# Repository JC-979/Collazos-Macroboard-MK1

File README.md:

# Collazos-Macroboard-MK1
This is the first Macroboard that i have made, and this made me interested on the all the hack club stuff, hope this project is just the beggining of a path with Blueprint
## Bom

- 9x Cherry MX Switches
- 3x SK6812 MINI Leds
- 1x XIAO RP2040
- 9x Blank DSA Keycaps
- 9x M3x16 Bolt
- 9x M3 Heatset

## Screenshots

## Overall Hackpad

- 
- 

## Schematics

- 

## PCB

- 

## Case

- 
- 
-

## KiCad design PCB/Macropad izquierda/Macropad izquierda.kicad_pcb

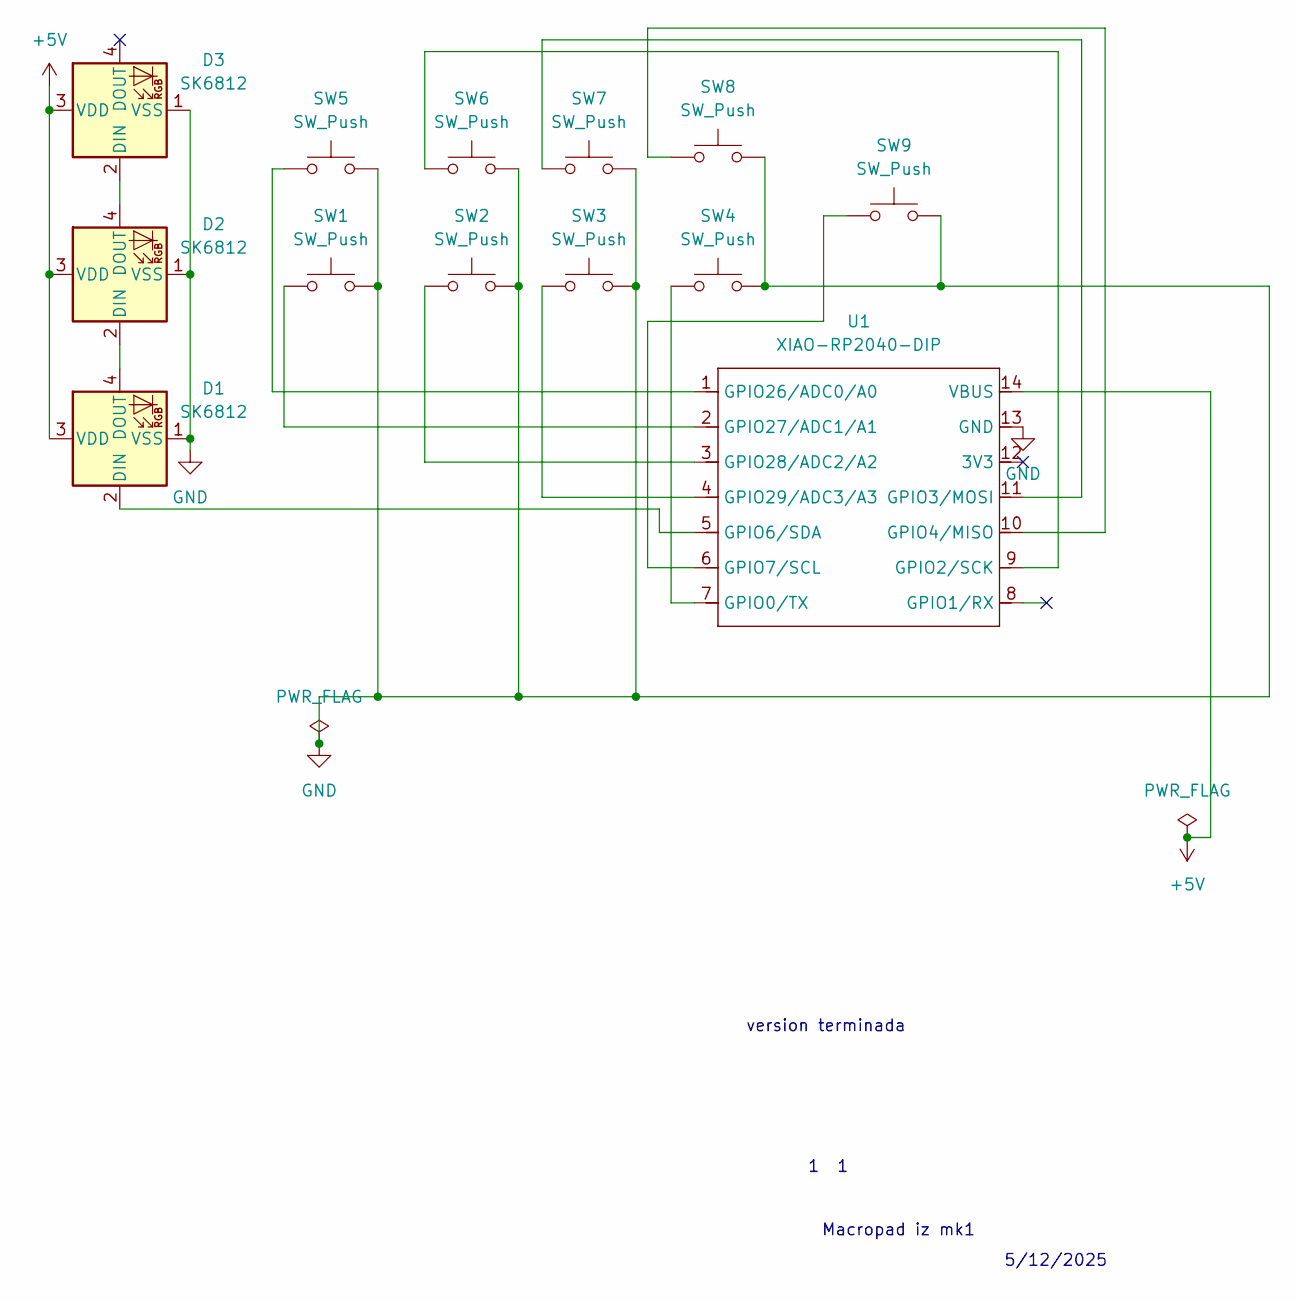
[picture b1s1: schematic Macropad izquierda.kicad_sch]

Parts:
D1, D2, D3: SK6812; LED_SK6812_PLCC4_5.0x5.0mm_P3.2mm
SW1, SW2, SW3, SW4, SW5, SW6, SW7, SW8, SW9: SW_Push; SW_Cherry_MX_1.00u_PCB
U1: XIAO-RP2040-DIP

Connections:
+5V: D1.3 (VDD), D2.3 (VDD), D3.3 (VDD), U1.14 (VBUS)
GND: D1.1 (VSS), D2.1 (VSS), D3.1 (VSS), SW1.2, SW2.2, SW3.2, SW4.2, SW5.2, SW6.2, SW7.2, SW8.2, SW9.2, U1.13 (GND)
unnamed: D1.2 (DIN), U1.5 (GPIO6/SDA)
unnamed: D1.4 (DOUT), D2.2 (DIN)
unnamed: D2.4 (DOUT), D3.2 (DIN)
unnamed: SW4.1, U1.7 (GPIO0/TX)
unnamed: SW6.1, U1.9 (GPIO2/SCK)
unnamed: SW7.1, U1.11 (GPIO3/MOSI)
unnamed: SW8.1, U1.10 (GPIO4/MISO)
unnamed: SW9.1, U1.6 (GPIO7/SCL)
unnamed: SW5.1, U1.1 (GPIO26/ADC0/A0)
unnamed: SW1.1, U1.2 (GPIO27/ADC1/A1)
unnamed: SW2.1, U1.3 (GPIO28/ADC2/A2)
unnamed: SW3.1, U1.4 (GPIO29/ADC3/A3)

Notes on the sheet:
Macropad iz mk1
version terminada
1 1
5/12/2025

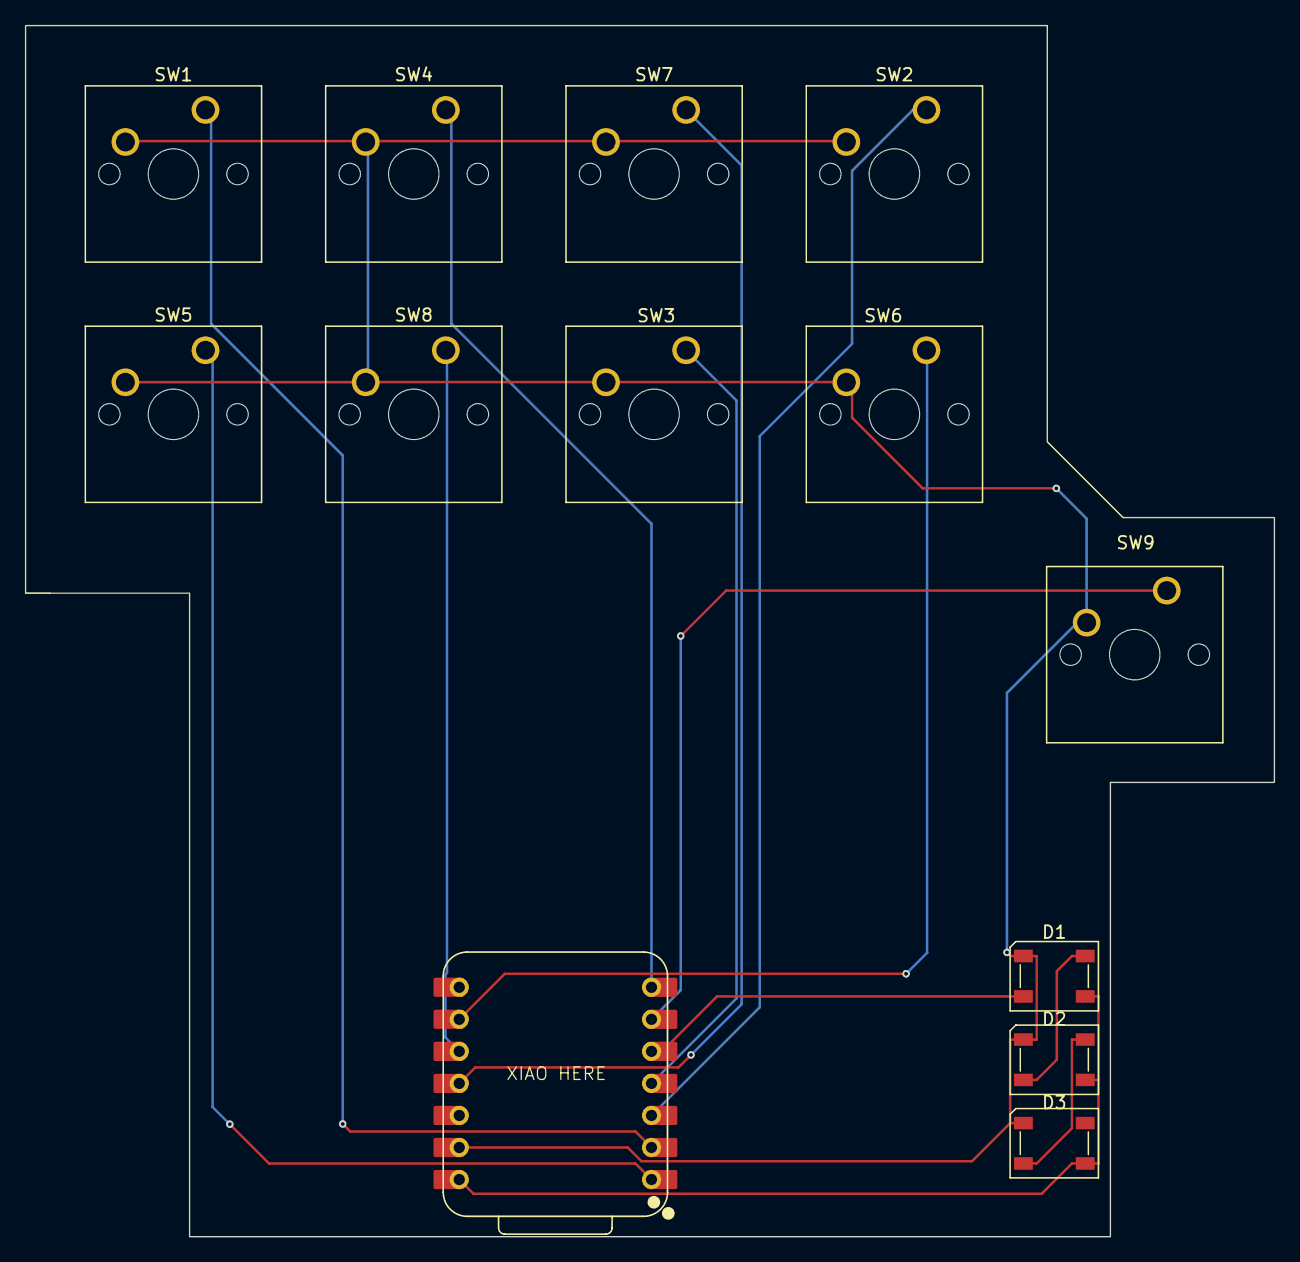
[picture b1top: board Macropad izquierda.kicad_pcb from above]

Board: 2 copper layers, 99.0 x 96.0 mm, 13 parts (0 on the bottom side), 14 nets.

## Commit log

2025-12-12 README.md
